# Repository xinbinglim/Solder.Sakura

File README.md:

# Solder.Sakura
Hellooooo, This is my first time to make a PCB! I tried to make a sakura umm but ends up it's not that cute:??? idk . It might have mistakes uhh and I tried new things! I never tried hardware before!<br><br>
Slack: @xinbinglim<br><br>

<br>I use:<br><br>
LED_SMD:LED_0805_2012Metric x5<br>
Resistor_THT:R_Axial_DIN0207_L6.3mm_D2.5mm_P7.62mm_Horizontal x 6<br>
OptoDevice:R_LDR_5.1x4.3mm_P3.4mm_Vertical x 1<br>
Battery:BatteryHolder_Keystone_3034_1x20mm x 1<br>
Package_TO_SOT_THT:TO-92L_HandSolder x 1<br>

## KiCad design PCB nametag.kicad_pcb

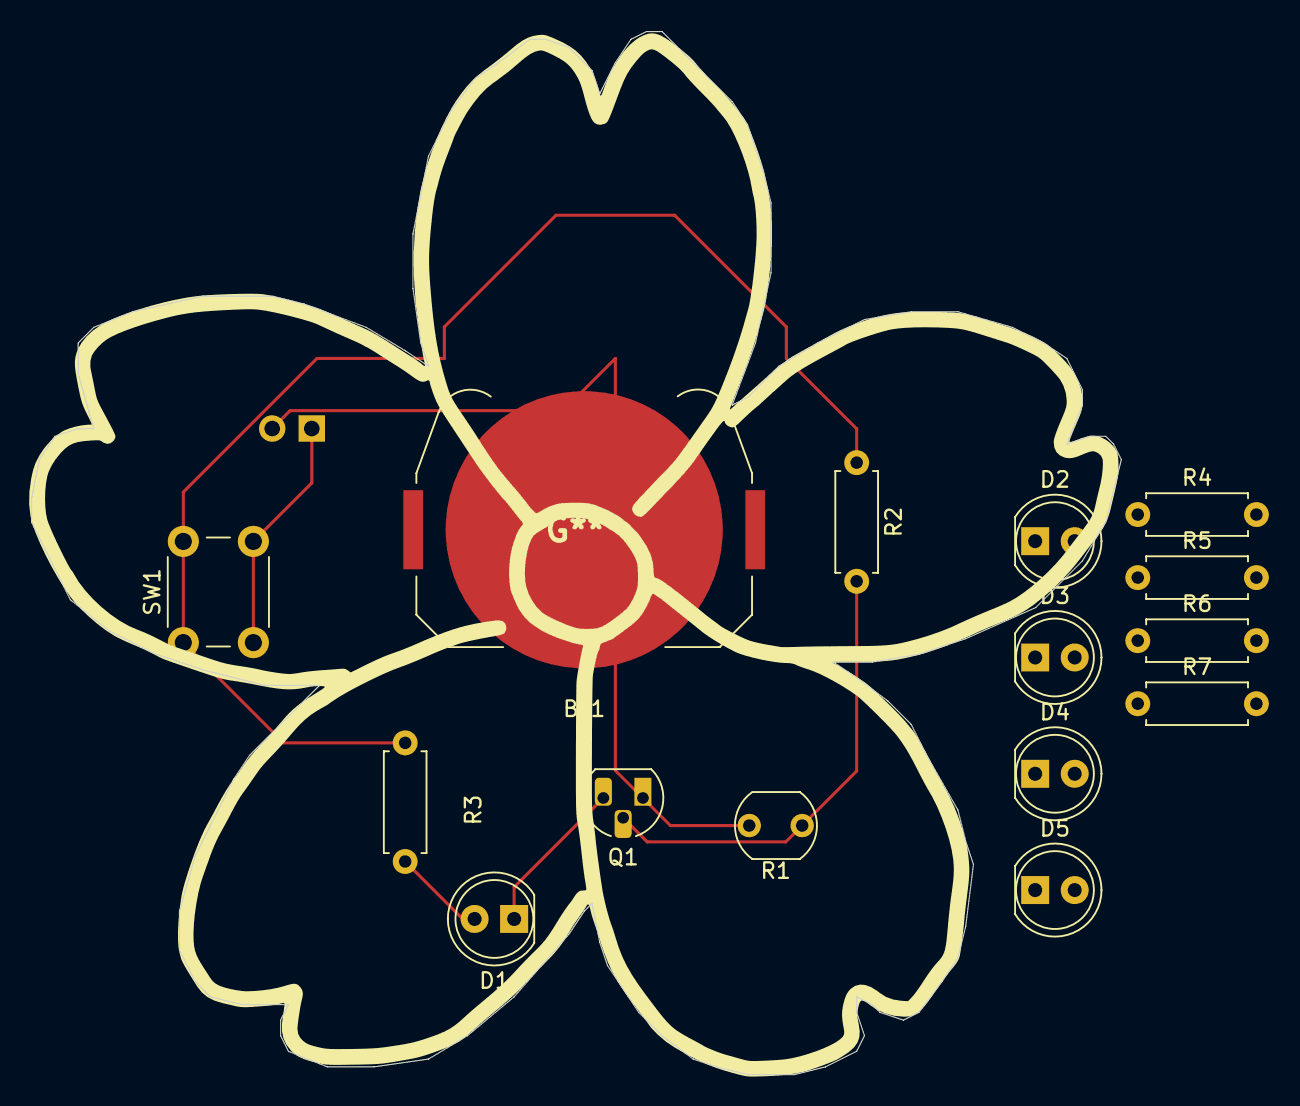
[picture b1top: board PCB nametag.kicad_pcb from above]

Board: 2 copper layers, 70.0 x 67.0 mm, 16 parts (1 on the bottom side), 10 nets.

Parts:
BT1: Battery_Cell; BatteryHolder_Keystone_3034_1x20mm
D1, D2, D3, D4, D5: LED; LED_D5.0mm
M1: Motor_DC; PinHeader_1x02_P2.54mm_Vertical
Q1: 2N3904; TO-92L_HandSolder
R1: R_Photo; R_LDR_5.1x4.3mm_P3.4mm_Vertical
R2, R3, R4, R5, R6, R7: R; R_Axial_DIN0207_L6.3mm_D2.5mm_P7.62mm_Horizontal
SW1: SW_Push; SW_PUSH_6mm

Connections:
unnamed: BT1.1 (+), R2.1, R3.1, R4.1, R5.1, R6.1, R7.1, SW1.1
unnamed: BT1.2 (-), M1.2 (-), Q1.3 (C), R1.2
unnamed: D1.2 (A), R3.2
unnamed: D1.1 (K), D2.1 (K), D3.1 (K), D4.1 (K), D5.1 (K), Q1.1 (E)
unnamed: D2.2 (A), R4.2
unnamed: D3.2 (A), R5.2
unnamed: D4.2 (A), R6.2
unnamed: D5.2 (A), R7.2
unnamed: M1.1 (+), SW1.2
unnamed: Q1.2 (B), R1.1, R2.2
